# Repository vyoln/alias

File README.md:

# alias
 First keyboard project/PCB

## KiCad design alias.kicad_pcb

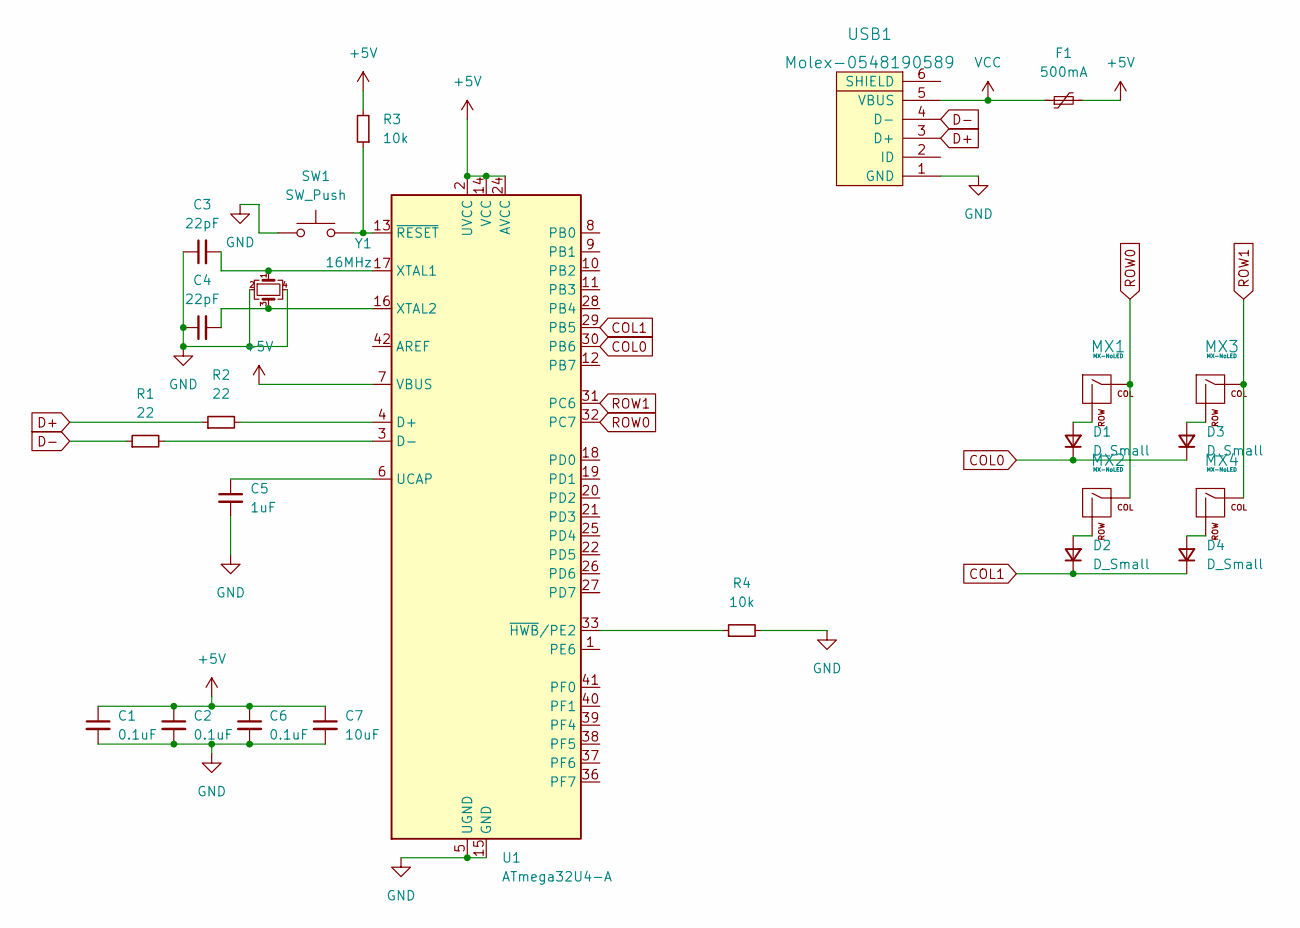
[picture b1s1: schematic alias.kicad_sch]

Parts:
C1, C2, C6: 0.1uF; C_0805_2012Metric
C3, C4: 22pF; C_0805_2012Metric
C5: 1uF; C_0805_2012Metric
C7: 10uF; C_0805_2012Metric
D1, D2, D3, D4: D_Small; D_SOD-123
F1: 500mA; Fuse_1206_3216Metric
MX1, MX2, MX3, MX4: MX-NoLED; MXOnly-1U-NoLED
R1, R2: 22; R_0805_2012Metric
R3, R4: 10k; R_0805_2012Metric
SW1: SW_Push; SKQG-1155865
U1: ATmega32U4-A; TQFP-44_10x10mm_P0.8mm
USB1: Molex-0548190589
Y1: 16MHz; Crystal_SMD_3225-4Pin_3.2x2.5mm

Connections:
+5V: C1.1, C2.1, C6.1, C7.1, F1.2, R3.2, U1.2 (UVCC), U1.7 (VBUS), U1.14 (VCC), U1.24 (AVCC), U1.34 (VCC), U1.44 (AVCC)
COL0: D1.1 (K), D3.1 (K), U1.30 (PB6)
COL1: D2.1 (K), D4.1 (K), U1.29 (PB5)
D+: R2.1, USB1.3 (D+)
D-: R1.1, USB1.4 (D-)
GND: C1.2, C2.2, C3.1, C4.1, C5.2, C6.2, C7.2, R4.2, SW1.1, U1.5 (UGND), U1.15 (GND), U1.23 (GND), U1.35 (GND), U1.43 (GND), USB1.1 (GND), Y1.2, Y1.4
unnamed: C3.2, U1.17 (XTAL1), Y1.1
unnamed: C4.2, U1.16 (XTAL2), Y1.3
unnamed: C5.1, U1.6 (UCAP)
unnamed: D1.2 (A), MX1.2 (ROW)
unnamed: D2.2 (A), MX2.2 (ROW)
unnamed: D3.2 (A), MX3.2 (ROW)
unnamed: D4.2 (A), MX4.2 (ROW)
unnamed: R1.2, U1.3 (D-)
unnamed: R2.2, U1.4 (D+)
unnamed: R3.1, SW1.2, U1.13 (~RESET)
unnamed: R4.1, U1.33 (~HWB/PE2)
ROW0: MX1.1 (COL), MX2.1 (COL), U1.32 (PC7)
ROW1: MX3.1 (COL), MX4.1 (COL), U1.31 (PC6)
VCC: F1.1, USB1.5 (VBUS)

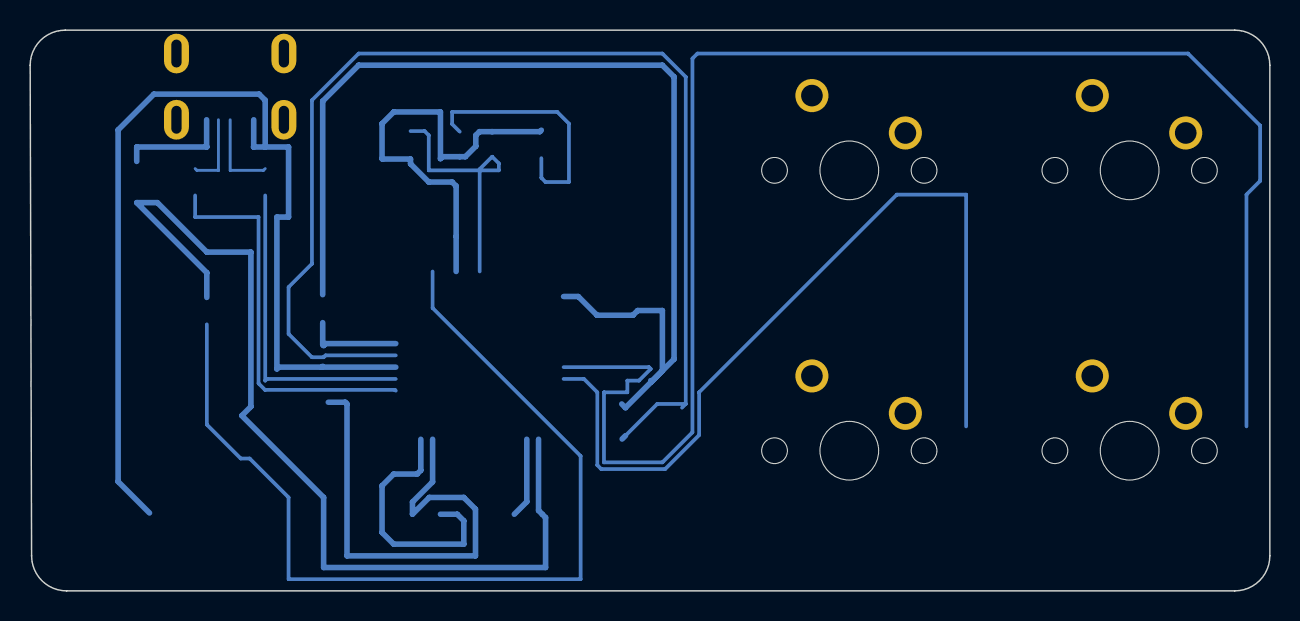
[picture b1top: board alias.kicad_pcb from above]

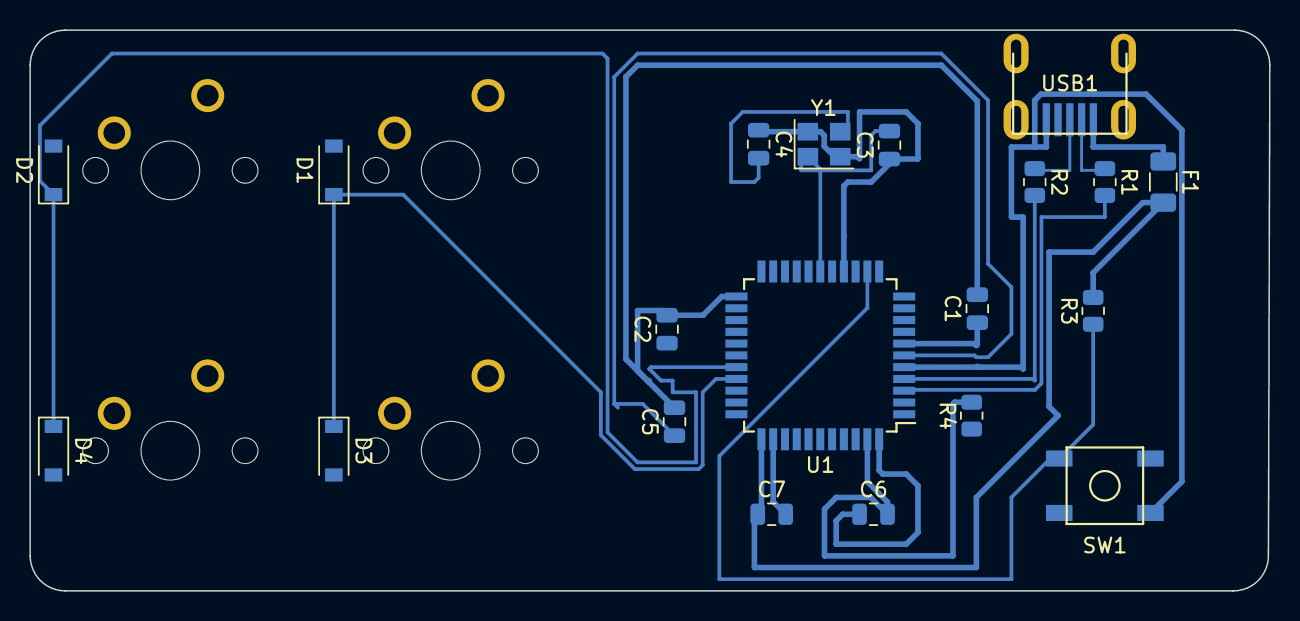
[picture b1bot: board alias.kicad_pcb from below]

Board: 2 copper layers, 84.2 x 38.1 mm, 24 parts (24 on the bottom side), 20 nets.

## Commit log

2022-12-01 Initialize KiCad Project
    Created KiCad project in repository
2022-12-01 Added submodules for KiCad (project-specific)
2022-12-01 Add footprint libraries for KiCad
2022-12-01 Changed PCB Schematic (Part 1 - Not Finished)
2022-12-02 Finished PCB Schematic
2022-12-02 Created PCB Layout
    Created PCB layout, need to do routing
2022-12-03 Added routing (not finished)
